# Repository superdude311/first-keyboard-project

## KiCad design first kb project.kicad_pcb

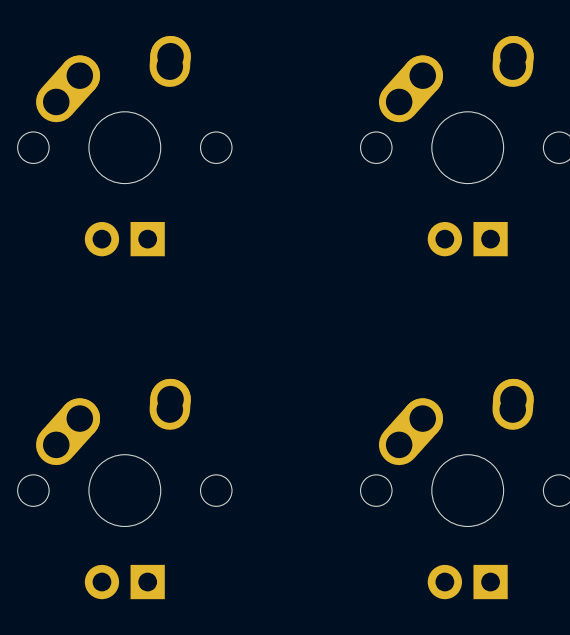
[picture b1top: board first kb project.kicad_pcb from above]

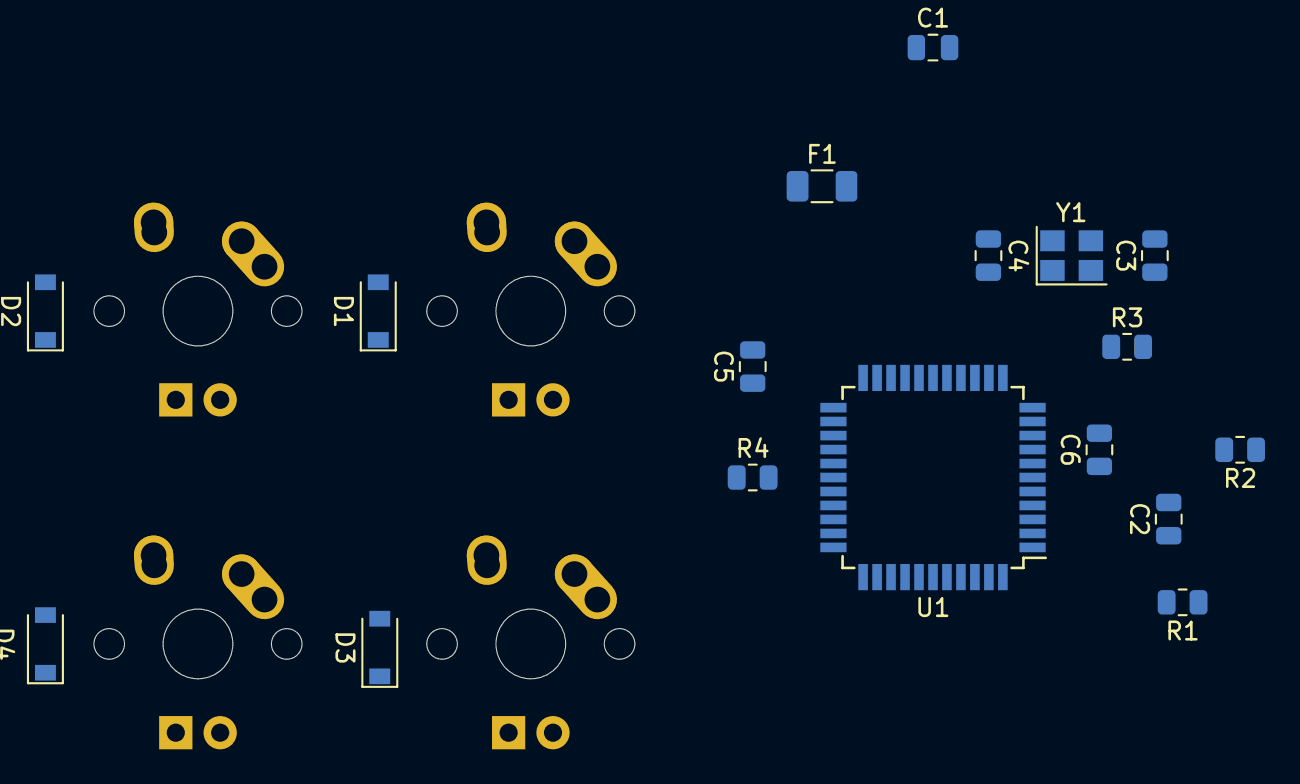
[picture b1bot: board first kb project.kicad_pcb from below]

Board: 2 copper layers, 21 parts (17 on the bottom side), 17 nets, no tracks yet.

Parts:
C1, C2, C5: 0.1uF; C_0805_2012Metric
C3, C4: 22pF; C_0805_2012Metric
C6: 1uF; C_0805_2012Metric
D1, D2, D3, D4: SOD-123; D_SOD-123
F1: 500mA; Fuse_1206_3216Metric
MX1, MX2, MX3, MX4: MX-NoLED; MX-1U
R1, R2: 22; R_0805_2012Metric
R3, R4: 10k; R_0805_2012Metric
U1: ATmega32U4-A; TQFP-44_10x10mm_P0.8mm
Y1: 16MHz; Crystal_SMD_3225-4Pin_3.2x2.5mm

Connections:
+5V: C1.1, C2.1, C5.1, F1.2, R3.1, U1.2 (UVCC), U1.7 (VBUS), U1.14 (VCC), U1.24 (AVCC), U1.34 (VCC), U1.44 (AVCC)
COL0: MX1.1 (COL), MX2.1 (COL)
COL1: MX3.1 (COL), MX4.1 (COL)
GND: C1.2, C2.2, C3.1, C4.1, C5.2, C6.1, R4.2, U1.5 (UGND), U1.15 (GND), U1.23 (GND), U1.35 (GND), U1.43 (GND), Y1.2, Y1.4
unnamed: C3.2, U1.17 (XTAL1), Y1.3
unnamed: C4.2, U1.16 (XTAL2), Y1.1
unnamed: C6.2, U1.6 (UCAP)
unnamed: D1.2 (A), MX1.2 (ROW)
unnamed: D2.2 (A), MX2.2 (ROW)
unnamed: D3.2 (A), MX3.2 (ROW)
unnamed: D4.2 (A), MX4.2 (ROW)
unnamed: R1.2, U1.4 (D+)
unnamed: R2.2, U1.3 (D-)
unnamed: R3.2, U1.13 (~RESET)
unnamed: R4.1, U1.33 (~HWB/PE2)
ROW0: D1.1 (K), D3.1 (K)
ROW1: D2.1 (K), D4.1 (K)

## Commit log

2022-01-22 Add submodules
2022-01-22 saving after library stuff
2022-01-22 finished schematic
    the molex and reset switch dont have footprints cuz the library thing is broken idek
2022-01-22 oh god (saving for the night)
    this is so dumb. the usb and switch footprints didnt work and now it doesnt have either of them on the pcb, not even my fault. im so done
